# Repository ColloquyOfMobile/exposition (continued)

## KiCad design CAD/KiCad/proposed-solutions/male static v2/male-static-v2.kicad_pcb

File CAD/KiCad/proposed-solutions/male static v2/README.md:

# Male static v2 — directly mounted GF1002 amplifier

## Manual placement reroute (2026-10-20)

`male-static-v2.kicad_pcb` is routed from the user's updated
`male-static-v2-placed.kicad_pcb`. All component positions, rotations, pad
nets and the artwork outline are retained. The socket runs horizontally;
the speaker connector is at (48.5, 89) mm. The 0.8 mm front-copper speaker
pair bends around C1, and photosensors C/D use reserved back-copper paths
along the left edge. Supply GND pours are refilled on both copper layers;
AUDIO_RETURN stays a separate net.

Native DRC reports **zero violations and zero unconnected items**. Schematic
parity reports the two supports H1/H2 missing, as in the edited placement;
they remain in the schematic. They have not been restored or relocated.
The placement's distant R1/R2/C2 positions are also retained: the earlier
short-input and close-decoupling geometry checks below do not describe this
layout. Physical fit, amplifier stability and noise have not been checked.

Current results are in `reports/validation.json` and `reports/drc.json`.
`preview.png`, `underside.png`, the STEP model, assembly SVG and production
Gerbers have been refreshed. The previous revision D notes below are design
history; their coordinates, support layout and route lengths are superseded.
`circuit.json` also records that earlier generated placement.

To reproduce this routing, run from the repository root:

```powershell
& 'C:/Program Files/KiCad/9.0/bin/python.exe' 'CAD/KiCad/old-reference/male static v2/scripts/route_placement.py'
& 'C:/Program Files/KiCad/9.0/bin/python.exe' export_gerbers.py
```

The route script uses the local Freerouting jar in `tmp/shields-tools/`.
The shared `build_boards.py`, `route_boards.py` and `verify_boards.py` still
describe the earlier generated revision D placement; rebuilding with them
would overwrite the manual placement or assert the earlier geometry.

## Earlier revision D design notes

All eleven connectors now have names on the front silkscreen: microphone,
DXL BODY, speaker, state LED, body/bar NeoPixels, harness, and photosensors
A/B/C/D (J9/J8/J1/J4). See
[`reports/connector-names.png`](<reports/connector-names.png>). Labels are shared
with the full board builder through `../female base v2/scripts/connector_labels.py`.

**C1 SMD update (2026-10-20).** C1 is now a polarized 220 µF / 10 V SMD
aluminium electrolytic in `Capacitor_SMD:CP_Elec_6.3x5.8`, centred at
(68.2, 71) mm. Pad 1 is positive / 5 V; pad 2 is GND. The 6.3 × 5.8 mm case
stays outside the module envelope. Local supply routing and ground fill have
been adjusted for its surface pads. C2 stays 100 nF / 0603. An example part
is [Panasonic EEEFN1A221UP](https://industrial.panasonic.com/ww/products/pt/aluminum-cap-smd/models/EEEFN1A221UP);
match the purchased part's land pattern and assembly requirements. The 220 µF
value remains provisional pending amplifier/harness measurements.

A second, continuous-wire schematic is available in
[`wired/male-static-v2-wired.pdf`](<wired/male-static-v2-wired.pdf>), with an
editable KiCad project beside it. It preserves revision D's circuit without
electrical labels. [`wired/comparison.md`](<wired/comparison.md>) explains each
element added since the original male static board and whether it is necessary.

Open `male-static-v2.kicad_pro` in KiCad 9. This new project includes the
schematic, routed PCB, assembled STEP model, previews, BOM and verification
reports. The original `../male static/` files are preserved.

The **GF1002 module itself** mounts on the main board; Thomas's perforated
prototype carrier is absent. **Specification (revision D, 2026-10-19): the
module plugs into a 1 × 11 female socket through male header pins on its
contact row**, as on the female base. The schematic and board files now implement **revision D**, with M1 as
the electrical socket, no JA1 hookup pads and no hand wires. The board is an
engineering prototype, subject to physical module and installation
measurements.

## Revision D: plug-in on header pins (2026-10-19)

Everything in `../female base v2/README.md` under revision D applies: the
socket, the module's headers, the pin-to-net table, height, supports, what
is removed, schematic and checks, the routing rules and the measurements
before ordering. At this board's coordinates:

- **Socket**: centre line at X = 58.55 mm (module origin (40, 55) + 18.55).
  Pin 1 is at the pot end at Y = 56.2 mm, and pin n at 56.2 + 2.54·(n − 1).
- **Supports**: H1 (37.5, 74.5) and H2 (50.1, 87.5) become supports at the
  measured stack height, about 11 mm. The pot then stands about **28 mm**
  above the board, 8 mm higher than revision C, and the shaft rises with
  it. Check both inside the male body.
- **Output**: J6 moved to (67,90), rotated −90 degrees. Its pin 2 is
  at (67,92.5). Both 0.8 mm front-copper paths are explicitly paired in
  the lower-right region, with a grounded guard on their input side.
- **Supply**: C2 is at (54.7,67.63), below socket pins 5 and 6 on the
  module side; the SMD C1 is at (68.2,71), outside the module envelope.
- **Input**: R1 is at (53,56.2), R2 at (54.8,58.74). The incoming line
  and return approach together on back copper from the upper board.

## Implemented layout and mechanical interface

The original 50 × 90 mm artwork outline, cutouts and exact DSUB pad/drill
positions are retained. Original connector pin orders are unchanged.
The module uses the same photo-derived 20.2 × 30 mm conservative envelope.
H1 and H2 retain their specified PCB hole positions. Their new insulating
support models have an 11 mm seat, a 1.8 mm module slot, short removable
retaining lips and a 3.2 × 2.2 mm screw slot for ±0.5 mm adjustment.
Select insulating M2 hardware and measure the actual socket/header stack
before printing/fitting the supports. No amplifier PCB drilling is required.

The socket's 8.5 mm body and nominal 2.5 mm header plastic put the module
underside at 11 mm and its PCB top at 12.6 mm above the carrier. Pot height
is approximately 28 mm; the shaft overhang is approximately 7 mm beyond
the board's left edge. Confirm both against the installed body.
Only low-profile divider/bypass parts sit under the module. The SMD C1
reservoir stays outside its envelope. All eleven socket pins are soldered;
module male headers populate positions 1–3, 5–6 and 8–11 only.

The socket alone occupies the contact strip. Native rule areas forbid
vias there; independent checks reject other components or pads in it.
The old pad-exclusion rule and flush-cut-pin instruction are removed.
To remove the amplifier, loosen the support lips and unplug the headers.

R1/R2 sit beside socket pins 1/2. C2 is less than 5 mm from both supply
contacts, with C1 nearby. Main supply and speaker routes use the 0.8 mm
Power width; short 0.25 mm necks enter the 0603 bypass pads. The input
pair approaches on back copper, with AMP_INPUT confined to the divider
and socket. A front grounded guard and ground pours separate the lower
output region from the input and sensor region. No output is grounded.

Speaker paths are 15.582/16.597 mm; the complete AMP_INPUT branch is 7.265 mm.
Independent checks find no parallel sensitive runs within 2.5 mm and no
output/input or sensor crossings in projection, including across layers.
Reports record geometry and source hashes in `reports/validation.json`.
Native ERC/DRC/unconnected/parity are all zero. These CAD checks do not
establish noise performance, current capacity or physical fit.

Inspect the updated STEP, previews and 1:1 templates before the mandatory
real-module fit, stack-height, ground-bond and output-polarity checks.

## Audio interface

| DSUB J7 pin | v2 function |
|---|---|
| 14 | LINE_IN, formerly remote amplifier speaker + |
| 7 | AUDIO_RETURN, formerly remote amplifier speaker − |
| 9 | Harness 5 V, unchanged |
| 1 and shell pads | Supply GND, unchanged |

The rack must be converted to **line-level audio and audio return** on the
former speaker pair. Disconnect its original class-D output from that pair
before using this board. J6 now goes only to the local GF1002 output:
pin 1 ROUT+, pin 2 ROUT−, with neither terminal connected to ground.

M1 follows the female board's socket table: pin 1 R input, 2 audio return,
5 harness 5 V, 6 supply GND, 10 provisional ROUT+, 11 provisional ROUT−.
Pins 3, 4, 7, 8 and 9 have no connections and schematic no-connect flags.
Confirm the actual ROUT pair polarity and module ground bond before ordering.

R1=22K/R2=3K3 reproduce Thomas's input divider. AUDIO_RETURN is routed
separately from the local supply GND pours; module-internal ground bonds
and return current behaviour need bench verification. The amplifier is
fed from harness **5 V only**; 12 V remains the servo rail. C1=220 µF/10 V
and C2=100 nF provide local decoupling. Reservoir sizing, the module's
actual supply rating, and shared harness current capacity remain to be
verified on the physical system.

## Regeneration and checks

The shared build, route, finish, export and verification scripts are in
`../female base v2/scripts/`. See that project's README for exact commands,
clamp assumptions, source attribution and assembly instructions.
`circuit.json` records component nets and positions; the unrouted placement
checkpoint is `male-static-v2-placed.kicad_pcb`. `reports/` contains native
ERC/DRC/parity results, netlist, schematic and assembly SVGs.

Native ERC and DRC, completed routing, schematic/PCB parity, retained original
outline/fixings/DSUB geometry, unchanged harness pin orders/drills, 5 V
amplifier connections and model resolution are checked. Exported STEP
assemblies were reopened and checked; top/underside previews inspected.
The module's undocumented internal circuit is outside ERC's scope.
Physical fit, acoustic/electrical operation and enclosure clearance have
not been established. No fabrication package is released at this stage.

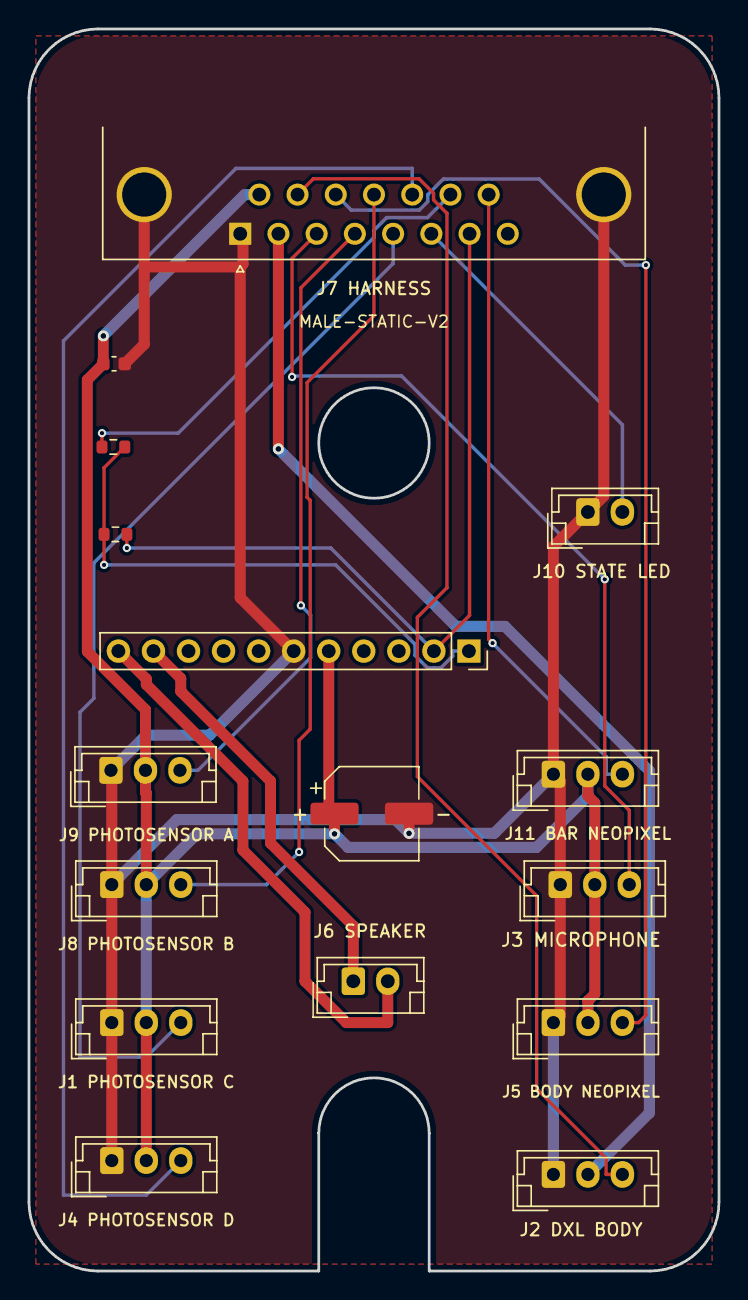
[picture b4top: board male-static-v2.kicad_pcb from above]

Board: 2 copper layers, 50.0 x 90.0 mm, 16 parts (0 on the bottom side), 17 nets.

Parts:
C1: 220uF 10V / provisional; CP_Elec_6.3x5.8
C2: 100nF; C_0603_1608Metric
J1: photosensor; J1_original
J2: dxl male; J2_original
J3: microphone; J3_original
J4: photosensor; J4_original
J5: body neopixel; J5_original
J6: Speaker; J6_original
J7: DA15_Plug_MountingHoles; J7_original
J8: photosensor; J8_original
J9: photosensor; J9_original
J10: State LED; J10_original
J11: bar neopixel; J11_original
M1: GF1002 / 1x11 female socket; GF1002_PlugIn_1x11
R1: 22K; R_0603_1608Metric
R2: 3K3; R_0603_1608Metric

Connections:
5V: C1.1, C2.1, J1.2, J3.2, J4.2, J5.2, J7.9, J8.2, J9.2, J11.2, M1.5
12V: J2.2, J7.2
AMP_INPUT: M1.1, R1.2, R2.1
AMP_OUT_N: J6.2, M1.11
AMP_OUT_P: J6.1, M1.10
AUDIO_RETURN: J7.7, M1.2, R2.2
GND: C1.2, C2.2, J1.1, J2.1, J3.1, J4.1, J5.1, J7.0, J7.1, J8.1, J9.1, J10.1, J11.1, M1.6
LINE_IN: J7.14, R1.1
bar neopixel male input: J7.15, J11.3
body neopixel male input: J5.3, J7.11
dynamixel data: J2.3, J7.10
microphone male output: J3.3, J7.3
photo sensor male output a: J7.4, J9.3
photo sensor male output b: J7.12, J8.3
photo sensor male output c: J1.3, J7.5
photo sensor male output d: J4.3, J7.13
state LED male output: J7.6, J10.2

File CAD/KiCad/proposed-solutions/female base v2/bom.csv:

Reference,Value,Footprint,Description
J4,photosensor,Body:J4_original,Original harness pin order retained. J6 now carries the local amplifier output.
J2,dxl mirror,Body:J2_original,Original harness pin order retained. J6 now carries the local amplifier output.
J7,DA15_Plug_MountingHoles,Body:J7_original,Original harness pin order retained. J6 now carries the local amplifier output.
J3,microphone,Body:J3_original,Original harness pin order retained. J6 now carries the local amplifier output.
J5,neopixel,Body:J5_original,Original harness pin order retained. J6 now carries the local amplifier output.
J6,Speaker,Body:J6_original,Original harness pin order retained. J6 now carries the local amplifier output.
R1,22K,Resistor_SMD:R_0603_1608Metric,
R2,3K3,Resistor_SMD:R_0603_1608Metric,
C1,220uF 10V / provisional,Capacitor_SMD:CP_Elec_6.3x5.8,"SMD polarized aluminium electrolytic, 6.3x5.8mm; pin 1 positive. Provisional local reservoir; verify actual amplifier transients and rail sag before release."
C2,100nF,Capacitor_SMD:C_0603_1608Metric,
M1,GF1002 / 1x11 female socket,Body:GF1002_PlugIn_1x11,"Plug-in module: 1x3, 1x2 and 1x4 downward male headers in an 11-pin female socket. Nominal underside gap 11mm. Pin 10=ROUT+, 11=ROUT- is provisional: verify module polarity before ordering."

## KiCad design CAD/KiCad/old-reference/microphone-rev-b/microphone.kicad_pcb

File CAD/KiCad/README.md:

# Electronics: designs, references and production

Use these four folders to distinguish the files' purpose:

| Folder | Contents |
| --- | --- |
| [proposed-solutions](proposed-solutions/) | Editable replacement designs, including selected boards and alternative designs. |
| [old-reference](old-reference/) | Original installation boards, superseded designs and historical exports. |
| [provided-elements](provided-elements/) | Reference models and footprints of purchased/provided modules and component datasheets. |
| [production](production/) | Current checked fabrication, JLCPCB assembly files, schematic SVGs and 45° PCB previews. |

The authoritative manufacture selection is `export_gerbers.py` at the repository root;
`production/manifest.json` records its exact source files and hashes. The server reads
this selection and refuses stale packages. Alternative designs are not manufacturing orders.

| Manufacture | Quantity |
| --- | ---: |
| Shields backplane | 1 |
| Teensy 4.1 adapter | 1 |
| Voice Thomas card | 5 |
| Analyser carrier | 1 |
| **Microphone flex holder, Rev C (32 × 62 mm)** | **6** |
| Female base v2 | 3 |
| Male static v2 | 2 |

The Rev B microphone holder is historical. Manufacture the Rev C **microphone-flex**
board with removable JP1/JP2 selectors and three alternative module orientations.
Fit one MAX9814 module per holder; see its README for initial selector settings and fit checks.

Order packages are under `production/assembly/<board>/`; the combined download is
`production/assembly/colloquy-production.zip`. Each board package contains `gerbers.zip`,
`BOM.csv` with exact manufacturer/LCSC identification, `CPL.csv`, and manual/DNP instructions.
The analyser carrier has no SMD population and is assembled by hand.

Regenerate from the repository root using KiCad's Python: `python export_jlcpcb.py`.
This checks DRC, produces the assembly packages, and refreshes browser assets.

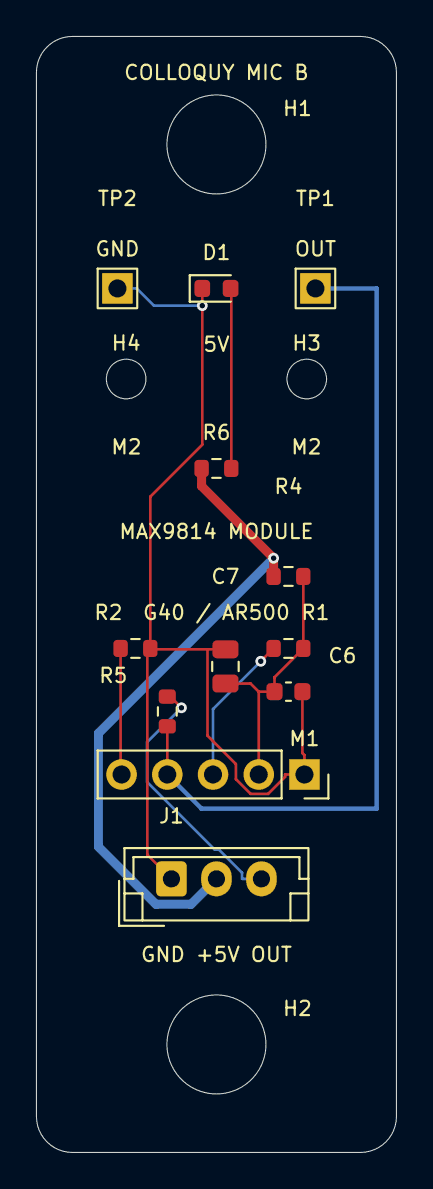
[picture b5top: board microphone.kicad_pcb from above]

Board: 2 copper layers, 20.0 x 62.0 mm, 16 parts (0 on the bottom side), 8 nets.

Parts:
C6: 100nF; C_0603_1608Metric
C7: 22uF X5R 10V; C_0805_2012Metric
D1: GREEN LED; LED_0603_1608Metric
H1, H2: M5 / 12mm copper keepout; MountingHole_5.5mm_Keepout12
H3, H4: M2 MODULE / INSULATING SPACER; MountingHole_2.2mm_M2_Keepout6
J1: GND / +5V / OUT; JST_EH_B3B-EH-A_1x03_P2.50mm_Vertical
M1: MAX9814 MODULE / 1x05 SOCKET; MAX9814_Module_Socket_1x05
R1: 0R / GAIN VDD 40dB; R_0603_1608Metric
R2: 0R / AR GND 1:500; R_0603_1608Metric
R4: 33R; R_0603_1608Metric
R5: 470R; R_0603_1608Metric
R6: 2K2; R_0603_1608Metric
TP1: MICOUT; TestPin_1x01_P2.54mm
TP2: GND; TestPin_1x01_P2.54mm

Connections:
+5V: J1.2, R4.1, R6.1
AR: M1.5, R2.1
GAIN: M1.3, R1.1
GND: C6.2, C7.2, D1.1, J1.1, M1.1, R2.2, TP2.1
MICOUT: M1.4, R5.1, TP1.1
OUT: J1.3, R5.2
VDD: C6.1, C7.1, M1.2, R1.2, R4.2
led/D1: D1.2, R6.2

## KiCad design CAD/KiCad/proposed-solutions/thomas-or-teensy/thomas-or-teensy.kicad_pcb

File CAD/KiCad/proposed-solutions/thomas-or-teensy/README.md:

# Colloquy — Thomas or Teensy

Open **`thomas-or-teensy.kicad_pro`** in KiCad 9. The native root schematic is
`thomas-or-teensy.kicad_sch`, and the main PCB is `thomas-or-teensy.kicad_pcb`.
The `-placed.kicad_pcb` is the preserved placement before routing. All schematic
symbols and footprints are project-local; no third-party KiCad plugin is needed.

This implements `Source code/Python/colloquy/hardware/electronics/THOMAS_OR_TEENSY.md`
in a separate project. Read **[REVIEW.md](<REVIEW.md>)** for the identified specification
problems, exact substitutions, verified pinouts and remaining hardware checks.
The v2 project and the original specification are not modified.

The board contains five SMD Thomas filter/MSGEQ7 channels, three PCM5102A DACs,
six buffered Teensy microphone inputs, three mode relays, two Teensy sockets,
bench connectors and protected MODE/UART crossings. The original harness,
Mega underside footprint, U2D2 mount and enclosure interface are preserved.
The finished PCB has **four copper layers at 1.6mm overall thickness**: signals
on the two outer layers and split AGND/GND planes on the two inner layers.
The preserved `-placed` file is the two-layer input to the routing stage.

`reports/schematic.pdf` and `reports/board-preview.png` are review views.
`reports/validation-summary.json`, ERC, DRC and connectivity reports record the
actual verification state; **a preview is not a fabrication release**. This is
a review prototype, and physical operation has not been tested.

## Assembly

- Fit the original fixed connectors, Mega mating headers underneath, and two
  24-way Teensy sockets on top. JT1/JT2 pin1 is at the USB end; follow GPIO names
  in the schematic, not socket pad numbers. Teensy gets its own USB power.
- Fit all three non-latching relays even for Thomas-only use. JM1 pins1–2 select
  Thomas, pins2–3 select Teensy; no shunt selects Thomas. Stop sound first.
- Fit MSGEQ7N SOIC-8 parts from an authorised source. JS1–JS5 stay **open**.
  The photosensor loads RP1–RP11 are provisional 10k in replaceable 1206 cases.
- Use PPS/C0G parts for the Thomas filters; the 470nF stages are three parallel
  parts each. Do not substitute X7R. Follow the PPS solder-paste and reflow limits.
- JP1 is the sole carrier AGND/GND bond. Do not add a second ground strap.
  Keep USB proposed-solutions/shields/external ground paths in mind during bench measurements.
- Bench output is line level for a powered speaker. The external body amplifier
  and its permitted rail are not selected by this board.
- `assembly/bom.csv` includes ordering descriptions and the plug-in Teensy/shunt.
  Common passives still require procurement choices meeting the stated package,
  value, dielectric, tolerance and voltage rating. Copper-only test points and
  open solder jumpers are not purchased components.

## Regeneration and checking

Native files can be edited normally. Scripts **do not preserve manual edits**;
use them only when deliberately regenerating this design. Use KiCad's bundled
Python for board scripts, and ordinary Python for `export_review.py`.

1. `build_design.py` writes the circuit contract and schematic.
2. `build_board.py` writes the separate `-placed` board and local footprints.
3. Call `build_design.schematic()` on the saved contract to update the schematic
   with the vendored footprint identifiers. Do not rebuild the original contract
   between placement and this call.
4. `route_board.py` takes explicit input/output paths, a local Freerouting JAR
   and Java runtime. It never overwrites its input. Routing is not validation.
5. `complete_routing.py` widens automatic neck-downs to 0.20mm, connects the
   two translator DIR supply branches, and routes the relay return around the
   analog region. Run it once on the fresh imported route; it changes copper.
   `route_coil_supply.py` moves the matching 2mm supply trunk around that region.
6. `route_clocks.py` brings the five I2S crossings beside JP1 and moves the
   clock test points alongside that crossing.
7. `finish_board.py` adds the two internal ground planes, fills the separate
   ground regions, assigns intentional NC
   nets and arranges silkscreen. Run final checks after any change to copper.
8. `check_design.py` runs seven independent interface/pinout/mechanical checks.
   `verify_schematic.py` compares exported native schematic nets with both the
   circuit contract and every PCB pad.
9. `audit_copper.py` measures widths and routing lengths;
   `check_clock_ground.py` samples the actual inner-plane coverage.
   `check_coil_supply.py` checks the physical supply path to all three coils.
   `export_review.py` refreshes the review package and records all findings.

Standard footprints derive from KiCad 9 under its library licence; see
`Colloquy.pretty/KICAD-LICENSE.md`. Fixed custom geometry comes from the v2
project. `PPS_6041` is drawn from Panasonic's recommended land pattern.
The preview lacks some custom/module 3D bodies, so it cannot establish fit.

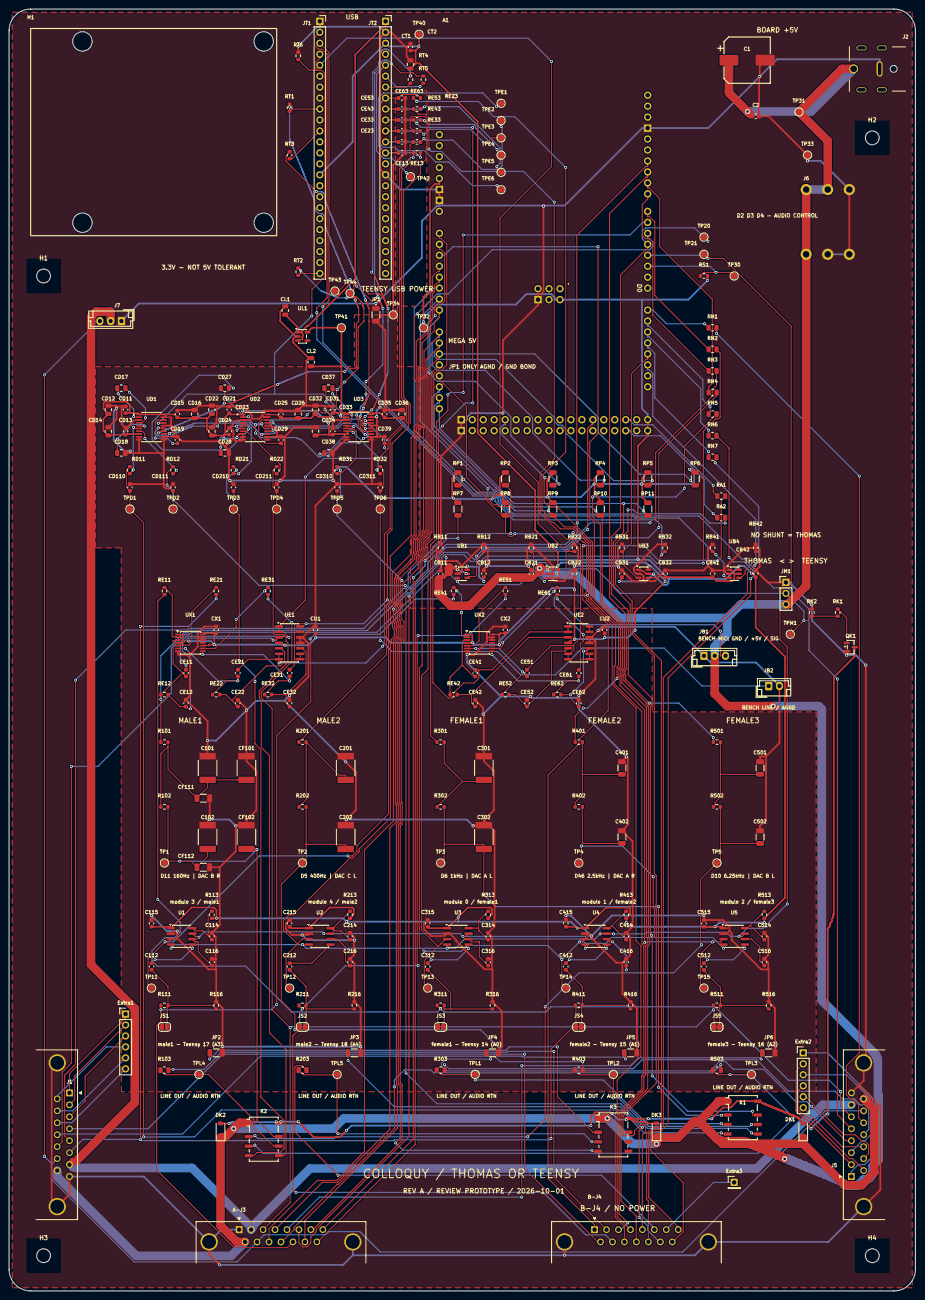
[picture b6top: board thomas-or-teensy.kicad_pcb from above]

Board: 4 copper layers, 210.0 x 297.0 mm, 290 parts (0 on the bottom side), 192 nets.

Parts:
A1: Arduino Mega 2560; Arduino_Mega2560_R3_Shield
A-J3: DSUB-15; DSUB-15_Pins_Horizontal_P2.77x2.84mm_EdgePinOffset4.94mm_Ho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
B-J4: DSUB-15; DSUB-15_Pins_Horizontal_P2.77x2.84mm_EdgePinOffset4.94mm_Ho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
C1: 470uF 25V; CP_Elec_10x10.5
C2, C112, C115, C116, C212, C215, C216, C312, C315, C316, C412, C415, C416, C512, C515, C516: 100nF; C_0603_1608Metric
C101, C102, C201, C202: 220nF PPS 5%; PPS_6041
C114, C214, C314, C414, C514: 33pF C0G; C_0603_1608Metric
C301, C302: 150nF PPS 5%; PPS_6041
C401, C402: 47nF C0G 5%; C_1206_3216Metric
C501, C502: 10nF C0G 5%; C_1206_3216Metric
CB11, CB12, CB21, CB22, CB31, CB32, CB41, CB42: 100nF; C_0603_1608Metric
CD11, CD13, CD15, CD19, CD21, CD23, CD25, CD29, CD31, CD33, CD35, CD39: 100nF; C_0603_1608Metric
CD12, CD14, CD16, CD22, CD24, CD26, CD32, CD34, CD36: 10uF; C_0805_2012Metric
CD17, CD18, CD27, CD28, CD37, CD38: 2.2uF; C_0805_2012Metric
CD110, CD111, CD210, CD211, CD310, CD311: 2.2nF C0G; C_0603_1608Metric
CE11, CE21, CE31, CE41, CE51, CE61: 2.2nF C0G; C_0603_1608Metric
CE12, CE13, CE22, CE23, CE32, CE33, CE42, CE43, CE52, CE53, CE62, CE63: 1nF C0G; C_0603_1608Metric
CF101, CF102: 220nF PPS 5%; PPS_6041
CF111, CF112: 30nF C0G 5%; C_1206_3216Metric
CL1, CL2: 10uF; C_0805_2012Metric
CT1: 100nF; C_0603_1608Metric
CT2: 10uF; C_0805_2012Metric
CU1, CU2: 100nF; C_0603_1608Metric
CX1, CX2: 100nF; C_0603_1608Metric
DK1, DK2, DK3: 1N4148W; D_SOD-123
Extra1, Extra2: 1x6 header; PinHeader_1x06_P2.54mm_Vertical
Extra3: 1x1 pad; PinHeader_1x01_P2.54mm_Vertical
H1, H2, H3, H4: M3 3.2mm NPTH; MountingHole_3.2mm_M3
J1, J5: DSUB-15; DSUB-15_Pins_Horizontal_P2.77x2.84mm_EdgePinOffset4.94mm_Ho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
J2: DC jack; PJ-082BH_jack_10A
J6: screw bridge; screw_brigde
J7: JST EH 3; JST_EH_B3B-EH-A_1x03_P2.50mm_Vertical
JB1: BENCH MIC GND +5V SIGNAL; JST_EH_B3B-EH-A_1x03_P2.50mm_Vertical
JB2: BENCH LINE / AGND; JST_EH_B2B-EH-A_1x02_P2.50mm_Vertical
JM1: THOMAS / MODE / TEENSY; PinHeader_1x03_P2.54mm_Vertical
JP1, JP2, JP3, JP4, JP5, JP6: 0R; R_1206_3216Metric
JS1, JS2, JS3, JS4, JS5: ATTEN BYPASS (OPEN); SolderJumper-2_P1.3mm_Open_RoundedPad1.0x1.5mm
JT1: Teensy 4.1 LEFT; PinSocket_1x24_P2.54mm_Vertical
JT2: Teensy 4.1 RIGHT; PinSocket_1x24_P2.54mm_Vertical
K1, K2, K3: G6K-2F-Y DC5; Relay_DPDT_Omron_G6K-2F-Y
M1: U2D2; u2d2_mounting
QK1: 2N7002; SOT-23
R101, R102, R501, R502: 2K2; R_0603_1608Metric
R103, R203, R303, R403, R503: 100R; R_0805_2012Metric
R111, R211, R311, R411, R511: 47K; R_0603_1608Metric
R113, R213, R313, R413, R513: 200K 1%; R_0603_1608Metric
R116, R216, R316, R416, R516: 6K8; R_0603_1608Metric
R201, R202: 2K; R_0603_1608Metric
R301, R302: 1K2; R_0603_1608Metric
R401, R402: 1K8; R_0603_1608Metric
RA1, RA2: 330R; R_0805_2012Metric
RB11, RB12, RB21, RB22, RB31, RB32, RB41, RB42: 100K; R_0603_1608Metric
RD11, RD12, RD21, RD22, RD31, RD32: 470R; R_0603_1608Metric
RE11, RE12, RE21, RE22, RE31, RE32, RE41, RE42, RE51, RE52, RE61, RE62: 10K 1%; R_0603_1608Metric
RE13, RE23, RE33, RE43, RE53, RE63: 100R; R_0603_1608Metric
RK1: 100R; R_0603_1608Metric
RK2: 100K; R_0603_1608Metric
RN1, RN2, RN3, RN4, RN5, RN6, RN7: 330R; R_0805_2012Metric
RP1, RP2, RP3, RP4, RP5, RP6, RP7, RP8, RP9, RP10, RP11: 10K provisional; R_1206_3216Metric
RS1: 10K; R_0603_1608Metric
RT1, RT2, RT3, RT4, RT5: 33R; R_0603_1608Metric
RT6: 10K; R_0603_1608Metric
TP1, TP2, TP3, TP4, TP5, TP11, TP12, TP13, TP14, TP15, TP20, TP21, TP30, TP31, TP32, TP33, TP34: test pad; TestPoint_Pad_D1.5mm
TP40: TEENSY_3V3; TestPoint_Pad_D1.5mm
TP41: DAC_3V3; TestPoint_Pad_D1.5mm
TP42: TEENSY_A8; TestPoint_Pad_D1.5mm
TP43: BCLK; TestPoint_Pad_D1.5mm
TP44: LRCLK; TestPoint_Pad_D1.5mm
TPD1: female1/dac; TestPoint_Pad_D1.5mm
TPD2: female2/dac; TestPoint_Pad_D1.5mm
TPD3: female3/dac; TestPoint_Pad_D1.5mm
TPD4: male1/dac; TestPoint_Pad_D1.5mm
TPD5: male2/dac; TestPoint_Pad_D1.5mm
TPD6: bench/dac; TestPoint_Pad_D1.5mm
TPE1: female1/adc; TestPoint_Pad_D1.5mm
TPE2: female2/adc; TestPoint_Pad_D1.5mm
TPE3: female3/adc; TestPoint_Pad_D1.5mm
TPE4: male1/adc; TestPoint_Pad_D1.5mm
TPE5: male2/adc; TestPoint_Pad_D1.5mm
TPE6: bench/adc; TestPoint_Pad_D1.5mm
TPL1: female1/selected; TestPoint_Pad_D1.5mm
TPL2: female2/selected; TestPoint_Pad_D1.5mm
TPL3: female3/selected; TestPoint_Pad_D1.5mm
TPL4: male1/selected; TestPoint_Pad_D1.5mm
TPL5: male2/selected; TestPoint_Pad_D1.5mm
TPM1: MODE; TestPoint_Pad_D1.5mm
U1, U2, U3, U4, U5: MSGEQ7N; SOIC-8_3.9x4.9mm_P1.27mm
UB1, UB2, UB3, UB4: SN74LVC1T45DBVR; SOT-23-6
UD1, UD2, UD3: PCM5102APWR; TSSOP-20_4.4x6.5mm_P0.65mm
UE1, UE2: MCP6004-I/SL; SOIC-14_3.9x8.7mm_P1.27mm
UL1: TLV75533PDBVR; SOT-23-5
UX1, UX2: TMUX1511PWR; TSSOP-14_4.4x5mm_P0.65mm

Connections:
+5V: A-J3.9, C1.1, C2.1, CB11.1, CB21.1, DK1.1, DK2.1, DK3.1, J1.15, J2.1, J5.15, J6.3, J6.5, J6.6, JB1.2, JM1.3, K1.1, K2.1, K3.1, TP31.1, UB1.1, UB1.5, UB2.1, UB2.5
+12V: A-J3.2, J1.7, J5.7, J7.2
AGND: C101.2, C102.2, C114.2, C115.2, C116.2, C201.2, C202.2, C214.2, C215.2, C216.2, C301.2, C302.2, C314.2, C315.2, C316.2, C401.2, C402.2, C414.2, C415.2, C416.2, C501.2, C502.2, C514.2, C515.2, C516.2, CD11.2, CD12.2, CD13.2, CD14.2, CD15.2, CD16.2, CD18.2, CD19.2, CD21.2, CD22.2, CD23.2, CD24.2, CD25.2, CD26.2, CD28.2, CD29.2, CD31.2, CD32.2, CD33.2, CD34.2, CD35.2, CD36.2, CD38.2, CD39.2, CD110.2, CD111.2, CD210.2, CD211.2, CD310.2, CD311.2, CE12.2, CE13.2, CE22.2, CE23.2, CE32.2, CE33.2, CE42.2, CE43.2, CE52.2, CE53.2, CE62.2, CE63.2, CF101.2, CF102.2, CF111.2, CF112.2, CL1.2, CL2.2, CU1.2, CU2.2, CX1.2, CX2.2, JB1.1, JB2.2, JP1.1, JP2.2, JP3.2, JP4.2, JP5.2, JP6.2, R116.2, R216.2, R316.2, R416.2, R516.2, RP1.2, RP2.2, RP3.2, RP4.2, RP5.2, RP6.2, RP7.2, RP8.2, RP9.2, RP10.2, RP11.2, TP34.1, U1.2, U2.2, U3.2, U4.2, U5.2, UD1.3, UD1.9, UD1.10, UD1.11, UD1.12, UD1.16, UD1.19, UD2.3, UD2.9, UD2.10, UD2.11, UD2.12, UD2.16, UD2.19, UD3.3, UD3.9, UD3.10, UD3.11, UD3.12, UD3.16, UD3.19, UE1.11, UE1.12, UE2.11, UE2.12, UL1.2, UX1.7, UX1.12, UX1.13, UX2.7, UX2.12, UX2.13
BCLK: RT5.2, TP43.1, UD1.13, UD2.13, UD3.13
BCLK_raw: JT2.6, RT5.1
COIL_GATE: QK1.1, RK1.2
COIL_LOW: DK1.2, DK2.2, DK3.2, K1.8, K2.8, K3.8, QK1.3
DAC_3V3: CD11.1, CD12.1, CD13.1, CD14.1, CD15.1, CD16.1, CD21.1, CD22.1, CD23.1, CD24.1, CD25.1, CD26.1, CD31.1, CD32.1, CD33.1, CD34.1, CD35.1, CD36.1, CL2.1, TP41.1, UD1.1, UD1.8, UD1.20, UD2.1, UD2.8, UD2.20, UD3.1, UD3.8, UD3.20, UL1.5
DAC_A/CAPM: CD17.2, UD1.4
DAC_A/CAPP: CD17.1, UD1.2
DAC_A/LDOO: CD19.1, UD1.18
DAC_A/VNEG: CD18.1, UD1.5
DAC_B/CAPM: CD27.2, UD2.4
DAC_B/CAPP: CD27.1, UD2.2
DAC_B/LDOO: CD29.1, UD2.18
DAC_B/VNEG: CD28.1, UD2.5
DAC_C/CAPM: CD37.2, UD3.4
DAC_C/CAPP: CD37.1, UD3.2
DAC_C/LDOO: CD39.1, UD3.18
DAC_C/VNEG: CD38.1, UD3.5
DAC_XSMT: JT1.4, RT6.1, UD1.17, UD2.17, UD3.17
GND: A1.GND1, A1.GND2, A1.GND3, A1.GND4, A1.GND5, A1.GND6, A-J3.0, A-J3.1, B-J4.0, C1.2, C2.2, CB11.2, CB12.2, CB21.2, CB22.2, CB31.2, CB32.2, CB41.2, CB42.2, CT1.2, CT2.2, J1.0, J1.8, J2.2, J5.0, J5.8, J6.1, J6.2, J6.4, J7.1, JM1.1, JP1.2, JT1.1, JT2.2, JT2.15, QK1.2, RB11.2, RB12.2, RB21.2, RB22.2, RB31.2, RB32.2, RB41.2, RB42.2, RK2.2, RT6.2, TP33.1, UB1.2, UB2.2, UB3.2, UB4.2
I2S_A: RT1.2, UD1.14
I2S_A_raw: JT1.9, RT1.1
I2S_B: RT2.2, UD2.14
I2S_B_raw: JT1.24, RT2.1
I2S_C: RT3.2, UD3.14
I2S_C_raw: JT1.11, RT3.1
LRCLK: RT4.2, TP44.1, UD1.15, UD2.15, UD3.15
LRCLK_raw: JT2.7, RT4.1
MEGA_5V: A1.5V1, A1.5V2, A1.5V3, A1.5V4, C115.1, C215.1, C315.1, C415.1, C515.1, CB12.1, CB31.1, CB42.1, R113.1, R213.1, R313.1, R413.1, R513.1, RS1.2, TP32.1, U1.1, U2.1, U3.1, U4.1, U5.1, UB1.6, UB3.1, UB3.5, UB4.6
MODE: JM1.2, RB11.1, RB21.1, RK1.1, RK2.1, TPM1.1, UB1.3, UB2.3
MODE_MEGA: A1.D30, RB12.1, UB1.4
MODE_TEENSY: JT1.5, RB22.1, UB2.4
TEENSY_3V3: CB22.1, CB32.1, CB41.1, CT1.1, CT2.1, CU1.1, CU2.1, CX1.1, CX2.1, JT1.15, JT2.3, TP40.1, UB2.6, UB3.6, UB4.1, UB4.5, UE1.4, UE2.4, UX1.1, UX1.4, UX1.10, UX1.14, UX2.1, UX2.4, UX2.10, UX2.14
TEENSY_A8: JT2.5, TP42.1
TEENSY_VIN: CL1.1, JT2.1, UL1.1, UL1.3
amp shutdown: A1.D2, RS1.1, TP30.1
analyser/reset: A1.D3, TP21.1, U1.7, U2.7, U3.7, U4.7, U5.7
analyser/strobe: A1.D4, TP20.1, U1.4, U2.4, U3.4, U4.4, U5.4
bench/adc: CE63.1, JT2.8, RE63.2, TPE6.1
bench/buffer: CE61.2, RE63.1, UE2.8, UE2.9
bench/dac: CD311.1, JB2.1, RD32.2, TPD6.1
bench/dac raw: RD32.1, UD3.7
bench/filter: CE62.1, RE62.2, UE2.10
bench/isolator in: RE61.2, UX2.9
bench/microphone: JB1.3, RE61.1
bench/mid: CE61.1, RE62.1, UX2.8
centre/spare1: B-J4.7, Extra3.1
dxl_data: A-J3.10, J1.14, J5.14, J7.3
female1/adc: CE13.1, JT2.13, RE13.2, TPE1.1
female1/analyser out: A1.A0, TP13.1, U3.3
female1/audio return: J5.4, JP4.1
female1/buffer: CE11.2, RE13.1, UE1.1, UE1.2
female1/dac: CD110.1, K1.4, RD11.2, TPD1.1
female1/dac raw: RD11.1, UD1.6
female1/filter: CE12.1, RE12.2, UE1.3
female1/filter mid: C301.1, R301.2, R302.1
female1/filter out: C302.1, K1.2, R302.2, TP3.1
female1/internal reference: C316.1, U3.6
female1/isolator in: RE11.2, UX1.2
female1/line out: J5.12, R303.2
female1/mic attenuated: C312.1, JS3.2, R311.2, R316.1
female1/microphone: J5.6, JS3.1, R311.1, RE11.1
female1/mid: CE11.1, RE12.1, UX1.3
female1/msgeq input: C312.2, U3.5
female1/neopixel: J5.13, RN1.2
female1/neopixel/driven: A1.D14, RN1.1
female1/oscillator: C314.1, R313.2, U3.8
female1/photosensor: A1.A5, J5.5, RP1.1
female1/selected: K1.3, R303.1, TPL1.1
female1/spare1: Extra2.1, J5.1
female1/spare2: Extra2.2, J5.2
female1/spare3: Extra2.3, J5.3
female1/spare4: Extra2.4, J5.9
female1/spare5: Extra2.5, J5.10
female1/spare6: Extra2.6, J5.11
female1/tone: A1.D6, R301.1
female2/adc: CE23.1, JT2.12, RE23.2, TPE2.1
female2/analyser out: A1.A1, TP14.1, U4.3
female2/audio return: J1.4, JP5.1
female2/buffer: CE21.2, RE23.1, UE1.6, UE1.7
female2/dac: CD111.1, K1.5, RD12.2, TPD2.1
female2/dac raw: RD12.1, UD1.7
female2/filter: CE22.1, RE22.2, UE1.5
female2/filter mid: C401.1, R401.2, R402.1
female2/filter out: C402.1, K1.7, R402.2, TP4.1
female2/internal reference: C416.1, U4.6
female2/isolator in: RE21.2, UX1.5
female2/line out: J1.12, R403.2
female2/mic attenuated: C412.1, JS4.2, R411.2, R416.1
female2/microphone: J1.6, JS4.1, R411.1, RE21.1
female2/mid: CE21.1, RE22.1, UX1.6
female2/msgeq input: C412.2, U4.5
female2/neopixel: J1.13, RN2.2
female2/neopixel/driven: A1.D7, RN2.1
female2/oscillator: C414.1, R413.2, U4.8
female2/photosensor: A1.A6, J1.5, RP2.1
female2/selected: K1.6, R403.1, TPL2.1
female2/spare1: Extra1.1, J1.1
female2/spare2: Extra1.2, J1.2
female2/spare3: Extra1.3, J1.3
female2/spare4: Extra1.4, J1.9
female2/spare5: Extra1.5, J1.10
female2/spare6: Extra1.6, J1.11
female2/tone: A1.D46, R401.1
female3/adc: CE33.1, JT2.11, RE33.2, TPE3.1
female3/analyser out: A1.A2, TP15.1, U5.3
female3/audio return: A-J3.5, JP6.1
female3/buffer: CE31.2, RE33.1, UE1.8, UE1.9
female3/dac: CD210.1, K2.4, RD21.2, TPD3.1
female3/dac raw: RD21.1, UD2.6
female3/filter: CE32.1, RE32.2, UE1.10
female3/filter mid: C501.1, R501.2, R502.1
female3/filter out: C502.1, K2.2, R502.2, TP5.1
female3/internal reference: C516.1, U5.6
female3/isolator in: RE31.2, UX1.9
female3/line out: A-J3.12, R503.2
female3/mic attenuated: C512.1, JS5.2, R511.2, R516.1
female3/microphone: A-J3.3, JS5.1, R511.1, RE31.1
female3/mid: CE31.1, RE32.1, UX1.8
female3/msgeq input: C512.2, U5.5
female3/neopixel: A-J3.11, RN3.2
female3/neopixel/driven: A1.D8, RN3.1
female3/oscillator: C514.1, R513.2, U5.8
female3/photosensor: A1.A7, A-J3.4, RP3.1
female3/selected: K2.3, R503.1, TPL3.1
female3/tone: A1.D10, R501.1
link/mega_tx: A1.D18, RB31.1, UB3.3
link/teensy_tx: JT1.3, RB41.1, UB4.3
link/to_mega: A1.D19, RB42.1, UB4.4
link/to_teensy: JT1.2, RB32.1, UB3.4
male1/adc: CE43.1, JT2.10, RE43.2, TPE4.1
male1/analyser out: A1.A3, TP11.1, U1.3
male1/audio return: B-J4.2, JP2.1
male1/aux: B-J4.1, RA1.2
male1/aux driven: A1.D24, RA1.1
male1/bar neopixel: B-J4.15, RN6.2
male1/bar neopixel/driven: A1.D16, RN6.1
male1/buffer: CE41.2, RE43.1, UE2.1, UE2.2
male1/dac: CD211.1, K2.5, RD22.2, TPD4.1
male1/dac raw: RD22.1, UD2.7
male1/filter: CE42.1, RE42.2, UE2.3
male1/filter mid: C101.1, CF101.1, CF111.1, R101.2, R102.1
male1/filter out: C102.1, CF102.1, CF112.1, K2.7, R102.2, TP1.1
male1/internal reference: C116.1, U1.6
male1/isolator in: RE41.2, UX2.2
male1/line out: B-J4.9, R103.2
male1/mic attenuated: C112.1, JS1.2, R111.2, R116.1
male1/microphone: A-J3.13, JS1.1, R111.1, RE41.1
male1/mid: CE41.1, RE42.1, UX2.3
male1/msgeq input: C112.2, U1.5
male1/neopixel: A-J3.6, RN4.2
male1/neopixel/driven: A1.D9, RN4.1
male1/oscillator: C114.1, R113.2, U1.8
male1/photosensor/A: A1.A8, A-J3.14, RP4.1
male1/photosensor/B: A1.A9, A-J3.7, RP5.1
male1/photosensor/C: A1.A10, A-J3.15, RP6.1
male1/photosensor/D: A1.A11, A-J3.8, RP7.1
male1/selected: K2.6, R103.1, TPL4.1
male1/tone: A1.D11, R101.1
male2/adc: CE53.1, JT2.9, RE53.2, TPE5.1
male2/analyser out: A1.A4, TP12.1, U2.3
male2/audio return: B-J4.14, JP3.1
male2/aux: B-J4.13, RA2.2
male2/aux driven: A1.D25, RA2.1
male2/bar neopixel: B-J4.8, RN7.2
male2/bar neopixel/driven: A1.D17, RN7.1
male2/buffer: CE51.2, RE53.1, UE2.6, UE2.7
male2/dac: CD310.1, K3.4, RD31.2, TPD5.1
male2/dac raw: RD31.1, UD3.6
male2/filter: CE52.1, RE52.2, UE2.5
male2/filter mid: C201.1, R201.2, R202.1
male2/filter out: C202.1, K3.2, R202.2, TP2.1
male2/internal reference: C216.1, U2.6
male2/isolator in: RE51.2, UX2.5
male2/line out: B-J4.6, R203.2
male2/mic attenuated: C212.1, JS2.2, R211.2, R216.1
male2/microphone: B-J4.10, JS2.1, R211.1, RE51.1
male2/mid: CE51.1, RE52.1, UX2.6
male2/msgeq input: C212.2, U2.5
male2/neopixel: B-J4.3, RN5.2
male2/neopixel/driven: A1.D15, RN5.1
male2/oscillator: C214.1, R213.2, U2.8
male2/photosensor/A: A1.A12, B-J4.11, RP8.1
male2/photosensor/B: A1.A13, B-J4.4, RP9.1
male2/photosensor/C: A1.A14, B-J4.12, RP10.1
male2/photosensor/D: A1.A15, B-J4.5, RP11.1
male2/selected: K3.3, R203.1, TPL5.1
male2/tone: A1.D5, R201.1
spare1/buffer: UE1.13, UE1.14
spare2/buffer: UE2.13, UE2.14

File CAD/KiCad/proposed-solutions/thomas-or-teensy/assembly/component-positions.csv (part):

Ref,Val,Package,PosX,PosY,Rot,Side
"A-J3","DSUB-15","DSUB-15_Pins_Horizontal_P2.77x2.84mm_EdgePinOffset4.94mm_Housed_MountingHolesOffset4.94mm",97.305000,-334.960000,0.000000,top
"A1","Arduino Mega 2560","Arduino_Mega2560_R3_Shield",141.160000,-53.320000,-90.000000,top
"B-J4","DSUB-15","DSUB-15_Pins_Horizontal_P2.77x2.84mm_EdgePinOffset4.94mm_Housed_MountingHolesOffset4.94mm",179.655000,-334.960000,0.000000,top
"C1","470uF 25V","CP_Elec_10x10.5",215.000000,-64.000000,0.000000,top
"C2","100nF","C_0603_1608Metric",217.000000,-77.000000,0.000000,top
"C101","220nF PPS 5%","PPS_6041",90.000000,-228.000000,90.000000,top
"C102","220nF PPS 5%","PPS_6041",90.000000,-244.000000,90.000000,top
"C112","100nF","C_0603_1608Metric",77.000000,-274.000000,90.000000,top
"C114","33pF C0G","C_0603_1608Metric",91.000000,-267.000000,90.000000,top
"C115","100nF","C_0603_1608Metric",77.000000,-264.000000,90.000000,top
"C116","100nF","C_0603_1608Metric",91.000000,-273.000000,90.000000,top
"C201","220nF PPS 5%","PPS_6041",122.000000,-228.000000,90.000000,top
"C202","220nF PPS 5%","PPS_6041",122.000000,-244.000000,90.000000,top
"C212","100nF","C_0603_1608Metric",109.000000,-274.000000,90.000000,top
"C214","33pF C0G","C_0603_1608Metric",123.000000,-267.000000,90.000000,top
"C215","100nF","C_0603_1608Metric",109.000000,-264.000000,90.000000,top
"C216","100nF","C_0603_1608Metric",123.000000,-273.000000,90.000000,top
"C301","150nF PPS 5%","PPS_6041",154.000000,-228.000000,90.000000,top
"C302","150nF PPS 5%","PPS_6041",154.000000,-244.000000,90.000000,top
"C312","100nF","C_0603_1608Metric",141.000000,-274.000000,90.000000,top
"C314","33pF C0G","C_0603_1608Metric",155.000000,-267.000000,90.000000,top
"C315","100nF","C_0603_1608Metric",141.000000,-264.000000,90.000000,top
"C316","100nF","C_0603_1608Metric",155.000000,-273.000000,90.000000,top
"C401","47nF C0G 5%","C_1206_3216Metric",186.000000,-228.000000,90.000000,top
"C402","47nF C0G 5%","C_1206_3216Metric",186.000000,-244.000000,90.000000,top
"C412","100nF","C_0603_1608Metric",173.000000,-274.000000,90.000000,top
"C414","33pF C0G","C_0603_1608Metric",187.000000,-267.000000,90.000000,top
"C415","100nF","C_0603_1608Metric",173.000000,-264.000000,90.000000,top
"C416","100nF","C_0603_1608Metric",187.000000,-273.000000,90.000000,top
"C501","10nF C0G 5%","C_1206_3216Metric",218.000000,-228.000000,90.000000,top
"C502","10nF C0G 5%","C_1206_3216Metric",218.000000,-244.000000,90.000000,top
"C512","100nF","C_0603_1608Metric",205.000000,-274.000000,90.000000,top
"C514","33pF C0G","C_0603_1608Metric",219.000000,-267.000000,90.000000,top
"C515","100nF","C_0603_1608Metric",205.000000,-264.000000,90.000000,top
"C516","100nF","C_0603_1608Metric",219.000000,-273.000000,90.000000,top
"CB11","100nF","C_0603_1608Metric",144.000000,-183.000000,90.000000,top
"CB12","100nF","C_0603_1608Metric",154.000000,-183.000000,90.000000,top
"CB21","100nF","C_0603_1608Metric",165.000000,-183.000000,90.000000,top
"CB22","100nF","C_0603_1608Metric",175.000000,-183.000000,90.000000,top
"CB31","100nF","C_0603_1608Metric",186.000000,-183.000000,90.000000,top
"CB32","100nF","C_0603_1608Metric",196.000000,-183.000000,90.000000,top
"CB41","100nF","C_0603_1608Metric",207.000000,-183.000000,90.000000,top
"CB42","100nF","C_0603_1608Metric",217.000000,-183.000000,90.000000,top
"CD11","100nF","C_0603_1608Metric",71.000000,-145.000000,90.000000,top
"CD12","10uF","C_0805_2012Metric",67.000000,-145.000000,90.000000,top
"CD13","100nF","C_0603_1608Metric",71.000000,-150.000000,90.000000,top
"CD14","10uF","C_0805_2012Metric",67.000000,-150.000000,90.000000,top
"CD15","100nF","C_0603_1608Metric",83.000000,-146.000000,90.000000,top
"CD16","10uF","C_0805_2012Metric",87.000000,-146.000000,90.000000,top
"CD17","2.2uF","C_0805_2012Metric",70.000000,-140.000000,0.000000,top
"CD18","2.2uF","C_0805_2012Metric",70.000000,-155.000000,0.000000,top
"CD19","100nF","C_0603_1608Metric",83.000000,-152.000000,90.000000,top
"CD21","100nF","C_0603_1608Metric",95.000000,-145.000000,90.000000,top
"CD22","10uF","C_0805_2012Metric",91.000000,-145.000000,90.000000,top
"CD23","100nF","C_0603_1608Metric",95.000000,-150.000000,90.000000,top
"CD24","10uF","C_0805_2012Metric",91.000000,-150.000000,90.000000,top
"CD25","100nF","C_0603_1608Metric",107.000000,-146.000000,90.000000,top
"CD26","10uF","C_0805_2012Metric",111.000000,-146.000000,90.000000,top
"CD27","2.2uF","C_0805_2012Metric",94.000000,-140.000000,0.000000,top
"CD28","2.2uF","C_0805_2012Metric",94.000000,-155.000000,0.000000,top
"CD29","100nF","C_0603_1608Metric",107.000000,-152.000000,90.000000,top
"CD31","100nF","C_0603_1608Metric",119.000000,-145.000000,90.000000,top
"CD32","10uF","C_0805_2012Metric",115.000000,-145.000000,90.000000,top
"CD33","100nF","C_0603_1608Metric",119.000000,-150.000000,90.000000,top
"CD34","10uF","C_0805_2012Metric",115.000000,-150.000000,90.000000,top
"CD35","100nF","C_0603_1608Metric",131.000000,-146.000000,90.000000,top
"CD36","10uF","C_0805_2012Metric",135.000000,-146.000000,90.000000,top
"CD37","2.2uF","C_0805_2012Metric",118.000000,-140.000000,0.000000,top
"CD38","2.2uF","C_0805_2012Metric",118.000000,-155.000000,0.000000,top
"CD39","100nF","C_0603_1608Metric",131.000000,-152.000000,90.000000,top
"CD110","2.2nF C0G","C_0603_1608Metric",72.000000,-163.000000,90.000000,top
"CD111","2.2nF C0G","C_0603_1608Metric",82.000000,-163.000000,90.000000,top
"CD210","2.2nF C0G","C_0603_1608Metric",96.000000,-163.000000,90.000000,top
"CD211","2.2nF C0G","C_0603_1608Metric",106.000000,-163.000000,90.000000,top
"CD310","2.2nF C0G","C_0603_1608Metric",120.000000,-163.000000,90.000000,top
"CD311","2.2nF C0G","C_0603_1608Metric",130.000000,-163.000000,90.000000,top
"CE11","2.2nF C0G","C_0603_1608Metric",85.000000,-206.000000,90.000000,top
"CE12","1nF C0G","C_0603_1608Metric",85.000000,-213.000000,90.000000,top
"CE13","1nF C0G","C_0603_1608Metric",135.000000,-85.480000,0.000000,top
"CE21","2.2nF C0G","C_0603_1608Metric",97.000000,-206.000000,90.000000,top
"CE22","1nF C0G","C_0603_1608Metric",97.000000,-213.000000,90.000000,top
"CE23","1nF C0G","C_0603_1608Metric",135.000000,-82.940000,0.000000,top
"CE31","2.2nF C0G","C_0603_1608Metric",109.000000,-206.000000,90.000000,top
"CE32","1nF C0G","C_0603_1608Metric",109.000000,-213.000000,90.000000,top
"CE33","1nF C0G","C_0603_1608Metric",135.000000,-80.400000,0.000000,top
"CE41","2.2nF C0G","C_0603_1608Metric",152.000000,-206.000000,90.000000,top
"CE42","1nF C0G","C_0603_1608Metric",152.000000,-213.000000,90.000000,top
"CE43","1nF C0G","C_0603_1608Metric",135.000000,-77.860000,0.000000,top
"CE51","2.2nF C0G","C_0603_1608Metric",164.000000,-206.000000,90.000000,top
"CE52","1nF C0G","C_0603_1608Metric",164.000000,-213.000000,90.000000,top
"CE53","1nF C0G","C_0603_1608Metric",135.000000,-75.320000,0.000000,top
"CE61","2.2nF C0G","C_0603_1608Metric",176.000000,-206.000000,90.000000,top
"CE62","1nF C0G","C_0603_1608Metric",176.000000,-213.000000,90.000000,top
"CE63","1nF C0G","C_0603_1608Metric",135.000000,-72.780000,0.000000,top
"CF101","220nF PPS 5%","PPS_6041",99.000000,-228.000000,90.000000,top
"CF102","220nF PPS 5%","PPS_6041",99.000000,-244.000000,90.000000,top
"CF111","30nF C0G 5%","C_1206_3216Metric",89.000000,-235.000000,0.000000,top
"CF112","30nF C0G 5%","C_1206_3216Metric",89.000000,-251.000000,0.000000,top
"CL1","10uF","C_0805_2012Metric",108.000000,-122.000000,90.000000,top
"CL2","10uF","C_0805_2012Metric",114.000000,-134.000000,90.000000,top
"CT1","100nF","C_0603_1608Metric",137.000000,-61.000000,90.000000,top
"CT2","10uF","C_0805_2012Metric",137.000000,-65.000000,90.000000,top
"CU1","100nF","C_0603_1608Metric",115.000000,-196.000000,90.000000,top
"CU2","100nF","C_0603_1608Metric",182.000000,-196.000000,90.000000,top
"CX1","100nF","C_0603_1608Metric",92.000000,-196.000000,90.000000,top
"CX2","100nF","C_0603_1608Metric",159.000000,-196.000000,90.000000,top
"DK1","1N4148W","D_SOD-123",228.000000,-312.000000,90.000000,top
"DK2","1N4148W","D_SOD-123",93.000000,-312.000000,90.000000,top
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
